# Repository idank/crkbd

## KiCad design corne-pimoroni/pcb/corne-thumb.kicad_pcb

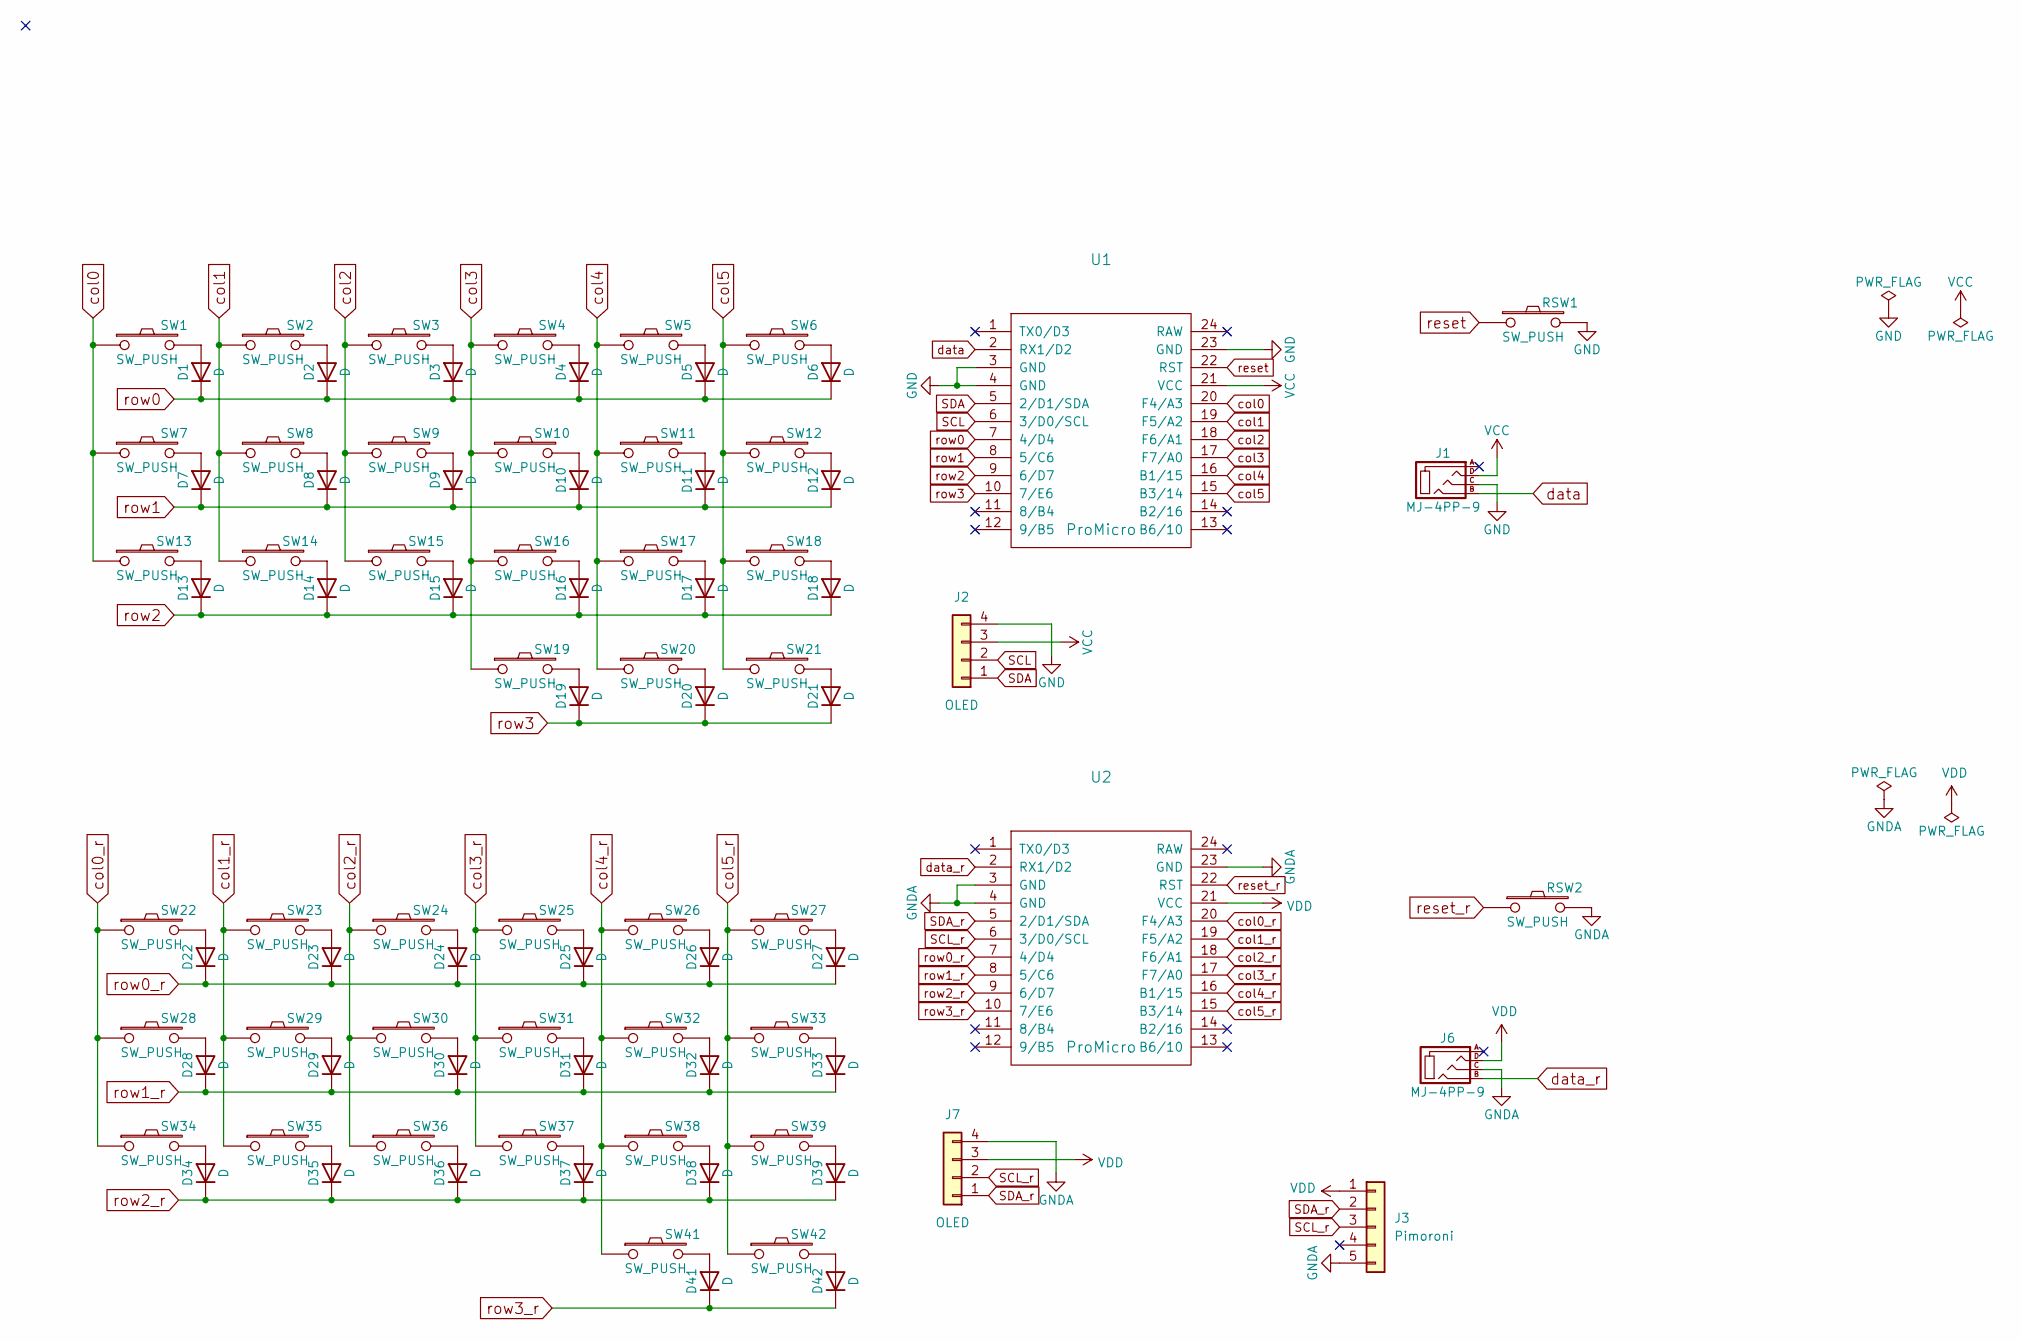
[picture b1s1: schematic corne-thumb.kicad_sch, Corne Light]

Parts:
D1, D2, D3, D4, D5, D6, D7, D8, D9, D10, D11, D12, D13, D14, D15, D16, D17, D18, D19, D20, D21, D22, D23, D24, D25, D26, D27, D28, D29, D30, D31, D32, D33, D34, D35, D36, D37, D38, D39, D41, D42: D; D3_TH
J1, J6: MJ-4PP-9; MJ-4PP-9_1side
J2, J7: OLED; OLED_1side
J3: Pimoroni; OLED_1side
RSW1, RSW2: SW_PUSH; ResetSW_1side
SW1, SW2, SW3, SW4, SW5, SW6, SW7, SW8, SW9, SW10, SW11, SW12, SW13, SW14, SW15, SW16, SW17, SW18, SW19, SW20, SW22, SW23, SW24, SW25, SW26, SW27, SW28, SW29, SW30, SW31, SW32, SW33, SW34, SW35, SW36, SW37, SW38, SW39, SW41: SW_PUSH; CherryMX_ChocV2_1u
SW21, SW42: SW_PUSH; CherryMX_ChocV2_1.5u
U1, U2: ProMicro; ProMicro_v3

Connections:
GND: J1.C, J2.4, RSW1.2, U1.3 (GND), U1.4 (GND), U1.23 (GND)
GNDA: J3.5, J6.C, J7.4, RSW2.2, U2.3 (GND), U2.4 (GND), U2.23 (GND)
unnamed: D1.2 (A), SW1.2
unnamed: D2.2 (A), SW2.2
unnamed: D3.2 (A), SW3.2
unnamed: D4.2 (A), SW4.2
unnamed: D5.2 (A), SW5.2
unnamed: D6.2 (A), SW6.2
unnamed: D7.2 (A), SW7.2
unnamed: D8.2 (A), SW8.2
unnamed: D9.2 (A), SW9.2
unnamed: D10.2 (A), SW10.2
unnamed: D11.2 (A), SW11.2
unnamed: D12.2 (A), SW12.2
unnamed: D13.2 (A), SW13.2
unnamed: D14.2 (A), SW14.2
unnamed: D15.2 (A), SW15.2
unnamed: D16.2 (A), SW16.2
unnamed: D17.2 (A), SW17.2
unnamed: D18.2 (A), SW18.2
unnamed: D19.2 (A), SW19.2
unnamed: D20.2 (A), SW20.2
unnamed: D21.2 (A), SW21.2
unnamed: D22.2 (A), SW22.2
unnamed: D23.2 (A), SW23.2
unnamed: D24.2 (A), SW24.2
unnamed: D25.2 (A), SW25.2
unnamed: D26.2 (A), SW26.2
unnamed: D27.2 (A), SW27.2
unnamed: D28.2 (A), SW28.2
unnamed: D29.2 (A), SW29.2
unnamed: D30.2 (A), SW30.2
unnamed: D31.2 (A), SW31.2
unnamed: D32.2 (A), SW32.2
unnamed: D33.2 (A), SW33.2
unnamed: D34.2 (A), SW34.2
unnamed: D35.2 (A), SW35.2
unnamed: D36.2 (A), SW36.2
unnamed: D37.2 (A), SW37.2
unnamed: D38.2 (A), SW38.2
unnamed: D39.2 (A), SW39.2
unnamed: D41.2 (A), SW41.2
unnamed: D42.2 (A), SW42.2
SCL: J2.2, U1.6 (3/D0/SCL)
SCL_r: J3.3, J7.2, U2.6 (3/D0/SCL)
SDA: J2.1, U1.5 (2/D1/SDA)
SDA_r: J3.2, J7.1, U2.5 (2/D1/SDA)
VCC: J1.D, J2.3, U1.21 (VCC)
VDD: J3.1, J6.D, J7.3, U2.21 (VCC)
col0: SW1.1, SW7.1, SW13.1, U1.20 (F4/A3)
col0_r: SW22.1, SW28.1, SW34.1, U2.20 (F4/A3)
col1: SW2.1, SW8.1, SW14.1, U1.19 (F5/A2)
col1_r: SW23.1, SW29.1, SW35.1, U2.19 (F5/A2)
col2: SW3.1, SW9.1, SW15.1, U1.18 (F6/A1)
col2_r: SW24.1, SW30.1, SW36.1, U2.18 (F6/A1)
col3: SW4.1, SW10.1, SW16.1, SW19.1, U1.17 (F7/A0)
col3_r: SW25.1, SW31.1, SW37.1, U2.17 (F7/A0)
col4: SW5.1, SW11.1, SW17.1, SW20.1, U1.16 (B1/15)
col4_r: SW26.1, SW32.1, SW38.1, SW41.1, U2.16 (B1/15)
col5: SW6.1, SW12.1, SW18.1, SW21.1, U1.15 (B3/14)
col5_r: SW27.1, SW33.1, SW39.1, SW42.1, U2.15 (B3/14)
data: J1.B, U1.2 (RX1/D2)
data_r: J6.B, U2.2 (RX1/D2)
reset: RSW1.1, U1.22 (RST)
reset_r: RSW2.1, U2.22 (RST)
row0: D1.1 (K), D2.1 (K), D3.1 (K), D4.1 (K), D5.1 (K), D6.1 (K), U1.7 (4/D4)
row0_r: D22.1 (K), D23.1 (K), D24.1 (K), D25.1 (K), D26.1 (K), D27.1 (K), U2.7 (4/D4)
row1: D7.1 (K), D8.1 (K), D9.1 (K), D10.1 (K), D11.1 (K), D12.1 (K), U1.8 (5/C6)
row1_r: D28.1 (K), D29.1 (K), D30.1 (K), D31.1 (K), D32.1 (K), D33.1 (K), U2.8 (5/C6)
row2: D13.1 (K), D14.1 (K), D15.1 (K), D16.1 (K), D17.1 (K), D18.1 (K), U1.9 (6/D7)
row2_r: D34.1 (K), D35.1 (K), D36.1 (K), D37.1 (K), D38.1 (K), D39.1 (K), U2.9 (6/D7)
row3: D19.1 (K), D20.1 (K), D21.1 (K), U1.10 (7/E6)
row3_r: D41.1 (K), D42.1 (K), U2.10 (7/E6)

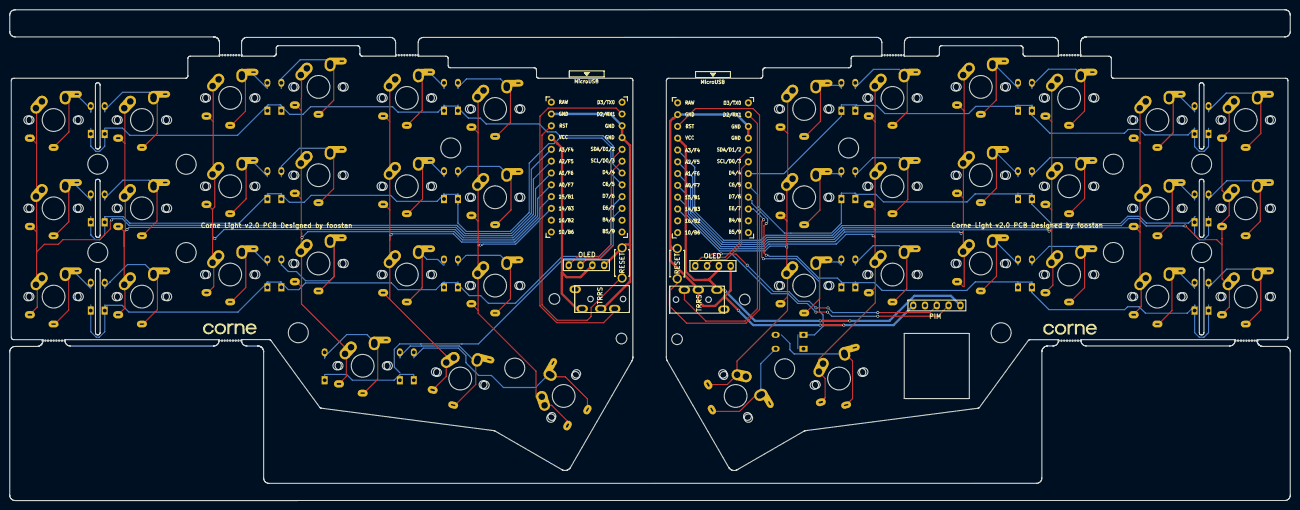
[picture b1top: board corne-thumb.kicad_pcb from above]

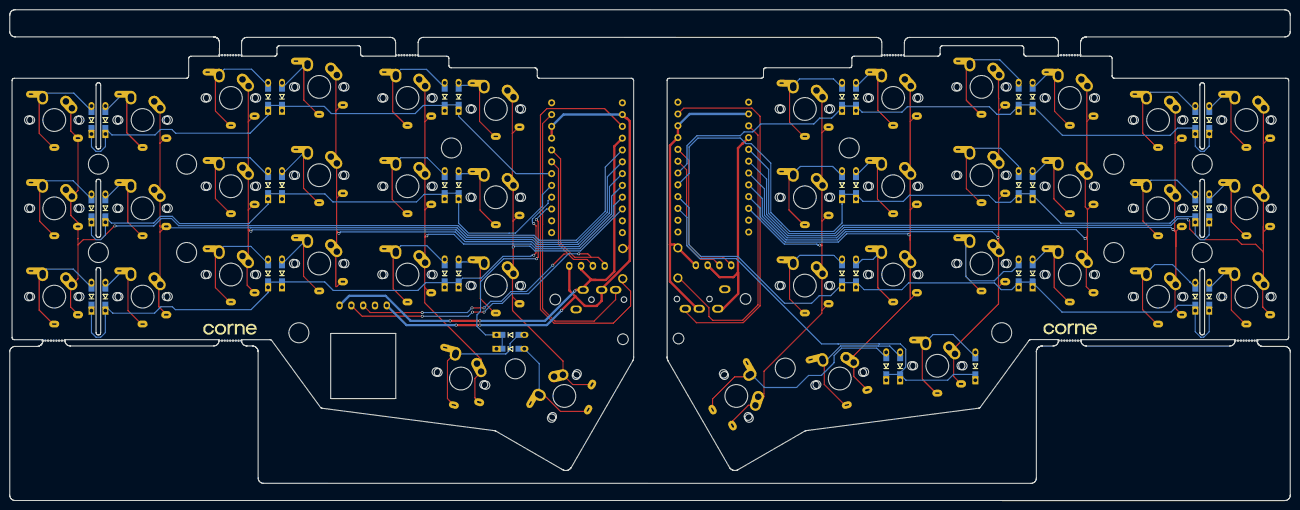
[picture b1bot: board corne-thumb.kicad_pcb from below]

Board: 2 copper layers, 275.5 x 105.6 mm, 117 parts (57 on the bottom side), 73 nets.

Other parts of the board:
J5, J5#2, J5#3, J5#4, J5#5, J5#6, J5#7, J5#8: Breakaway_Tabs
Ref**: Val**; thread_m2
Ref**#2, Ref**#8, Ref**#9: Val**; thread_m2
Ref**#3, Ref**#4, Ref**#5, Ref**#6, Ref**#7, Ref**#10, Ref**#11, Ref**#12, Ref**#13, Ref**#14, Ref**#15, Ref**#16, Ref**#17, Ref**#18: Val**; spacer_m2

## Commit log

2023-02-11 add corne light variant with thumb pimoroni on right side
